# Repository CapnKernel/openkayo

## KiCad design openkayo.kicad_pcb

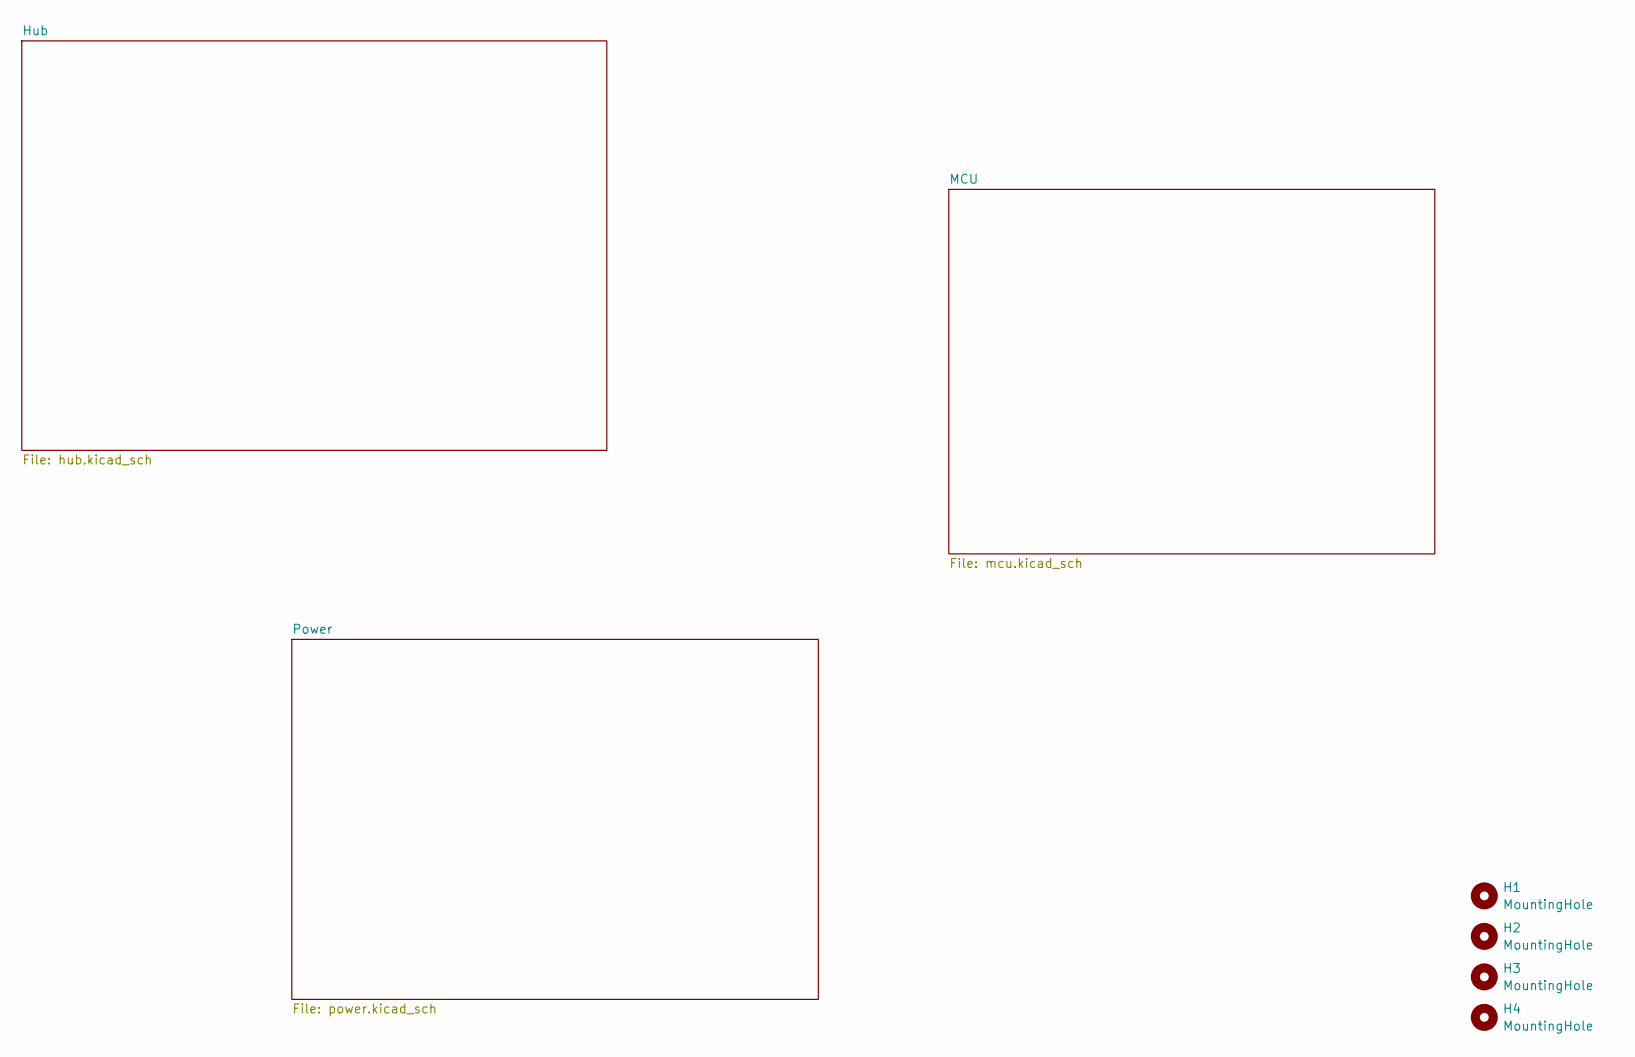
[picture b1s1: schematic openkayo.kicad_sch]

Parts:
H1, H2, H3, H4: MountingHole; MountingHole_3.2mm_M3

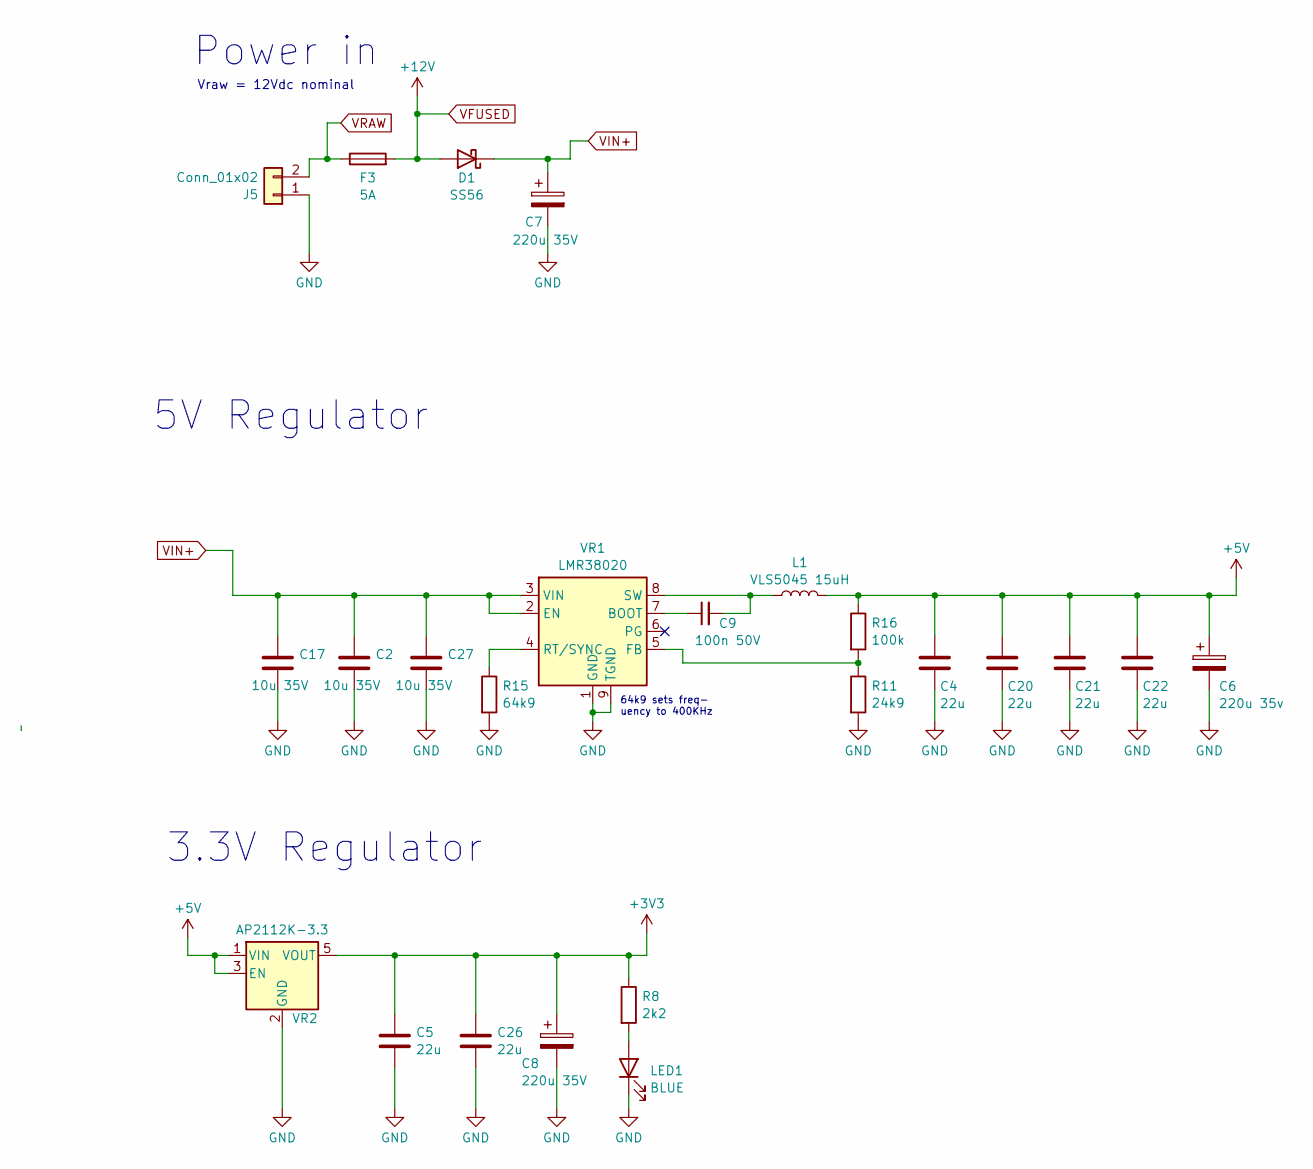
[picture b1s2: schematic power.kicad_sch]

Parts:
C2, C17, C27: 10u 35V; C_0805_2012Metric
C4, C5, C20, C21, C22, C26: 22u; C_0805_2012Metric
C6: 220u 35v; CP_Elec_8x10
C7, C8: 220u 35V; CP_Elec_8x10
C9: 100n 50V; C_0603_1608Metric
D1: SS56; D_SMA
F3: 5A; Fuseholder_Blade
J5: Conn_01x02; TerminalBlock_MetzConnect_Type086_RT03402HBLC_1x02_P3.81mm_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
L1: VLS5045 15uH; L_TDK_VLS6045EX_VLS6045AF
LED1: BLUE; LED_0603_1608Metric
R8: 2k2; R_0603_1608Metric
R11: 24k9; R_0603_1608Metric
R15: 64k9; R_0805_2012Metric
R16: 100k; R_0805_2012Metric
VR1: LMR38020; Texas_HSOP-8-1EP_3.9x4.9mm_P1.27mm_ThermalVias
VR2: AP2112K-3.3; SOT-23-5

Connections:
+3V3: C5.1, C8.1, C26.1, R8.1, VR2.5 (VOUT); also elsewhere on the board
+5V: C4.1, C6.1, C20.1, C21.1, C22.1, L1.2, R16.1, VR2.1 (VIN), VR2.3 (EN); also elsewhere on the board
GND: C2.2, C4.2, C5.2, C6.2, C7.2, C8.2, C17.2, C20.2, C21.2, C22.2, C26.2, C27.2, J5.1, LED1.1 (K), R11.2, R15.2, VR1.1 (GND), VR1.9 (TGND), VR2.2 (GND); also elsewhere on the board
unnamed: LED1.2 (A), R8.2
unnamed: C9.1, VR1.7 (BOOT)
unnamed: R11.1, R16.2, VR1.5 (FB)
unnamed: R15.1, VR1.4 (RT/SYNC)
unnamed: C9.2, L1.1, VR1.8 (SW)
VFUSED: D1.2 (A), F3.2; also elsewhere on the board
VIN+: C2.1, C7.1, C17.1, C27.1, D1.1 (K), VR1.2 (EN), VR1.3 (VIN)
VRAW: F3.1, J5.2

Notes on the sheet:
64k9 sets freq- uency to 400KHz
Power in
3.3V Regulator
5V Regulator
Vraw = 12Vdc nominal

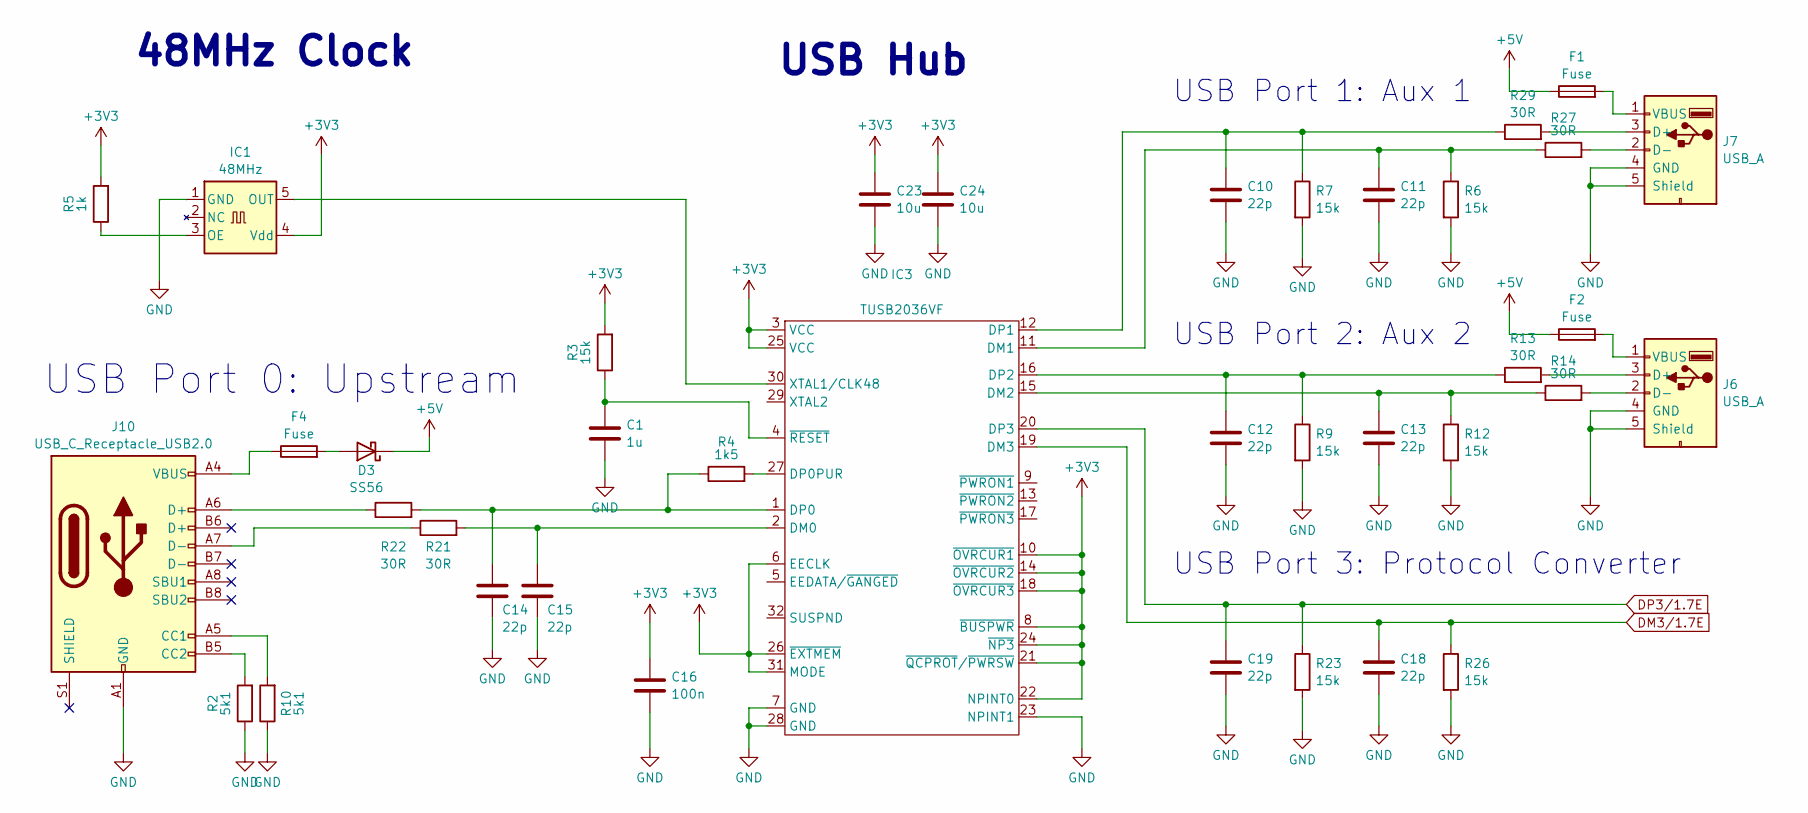
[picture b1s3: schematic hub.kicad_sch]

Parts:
C1: 1u; C_0603_1608Metric
C10, C11, C12, C13, C14, C15: 22p; C_0603_1608Metric
C16: 100n; C_0805_2012Metric
C18, C19: 22p; C_0402_1005Metric
C23, C24: 10u; C_0805_2012Metric
D3: SS56; D_SMA
F1, F2, F4: Fuse; Fuse_2018_5045Metric
IC1: 48MHz; SOT-23-5
IC3: TUSB2036VF; LQFP-32_7x7mm_P0.8mm
J6, J7: USB_A; USB_A_CONNFLY_DS1095-WNR0
J10: USB_C_Receptacle_USB2.0; USB_C_Receptacle_Amphenol_12401610E4-2A
R2, R10: 5k1; R_0603_1608Metric
R3, R6, R7, R9, R12: 15k; R_0603_1608Metric
R4: 1k5; R_0603_1608Metric
R5: 1k; R_0603_1608Metric
R13, R14, R27, R29: 30R; R_0603_1608Metric
R21, R22: 30R; R_0805_2012Metric
R23, R26: 15k; R_0805_2012Metric

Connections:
+3V3: C16.1, C23.1, C24.1, IC1.4 (Vdd), IC3.3 (VCC), IC3.6 (EECLK), IC3.8 (~BUSPWR), IC3.10 (~OVRCUR1), IC3.14 (~OVRCUR2), IC3.18 (~OVRCUR3), IC3.21 (~QCPROT/~PWRSW), IC3.22 (NPINT0), IC3.24 (~NP3), IC3.25 (VCC), IC3.26 (~EXTMEM), IC3.31 (MODE), R3.2, R5.2; also elsewhere on the board
+5V: D3.1 (K), F1.1, F2.1; also elsewhere on the board
DM3/1.7E: C18.1, IC3.19 (DM3), R26.1; also elsewhere on the board
DP3/1.7E: C19.1, IC3.20 (DP3), R23.1; also elsewhere on the board
GND: C1.2, C10.2, C11.2, C12.2, C13.2, C14.2, C15.2, C16.2, C18.2, C19.2, C23.2, C24.2, IC1.1 (GND), IC3.7 (GND), IC3.23 (NPINT1), IC3.28 (GND), J6.4 (GND), J6.5 (Shield), J7.4 (GND), J7.5 (Shield), J10.A1 (GND), J10.A12 (GND), J10.B1 (GND), J10.B12 (GND), R2.1, R6.2, R7.2, R9.2, R10.1, R12.2, R23.2, R26.2; also elsewhere on the board
unnamed: D3.2 (A), F4.2
unnamed: F4.1, J10.A4 (VBUS), J10.A9 (VBUS), J10.B4 (VBUS), J10.B9 (VBUS)
unnamed: IC1.3 (OE), R5.1
unnamed: IC1.5 (OUT), IC3.30 (XTAL1/CLK48)
unnamed: C15.1, IC3.2 (DM0), R21.2
unnamed: C11.1, IC3.11 (DM1), R6.1, R27.1
unnamed: C13.1, IC3.15 (DM2), R12.1, R14.1
unnamed: C14.1, IC3.1 (DP0), R4.1, R22.2
unnamed: IC3.27 (DP0PUR), R4.2
unnamed: C10.1, IC3.12 (DP1), R7.1, R29.1
unnamed: C12.1, IC3.16 (DP2), R9.1, R13.1
unnamed: C1.1, IC3.4 (~RESET), R3.1
unnamed: J6.3 (D+), R13.2
unnamed: J6.2 (D-), R14.2
unnamed: F2.2, J6.1 (VBUS)
unnamed: J7.3 (D+), R29.2
unnamed: J7.2 (D-), R27.2
unnamed: F1.2, J7.1 (VBUS)
unnamed: J10.A5 (CC1), R10.2
unnamed: J10.B5 (CC2), R2.2
unnamed: J10.A6 (D+), R22.1
unnamed: J10.A7 (D-), R21.1

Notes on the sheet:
48MHz Clock
USB Port 0: Upstream
USB Port 3: Protocol Converter
USB Hub
USB Port 2: Aux 2
USB Port 1: Aux 1

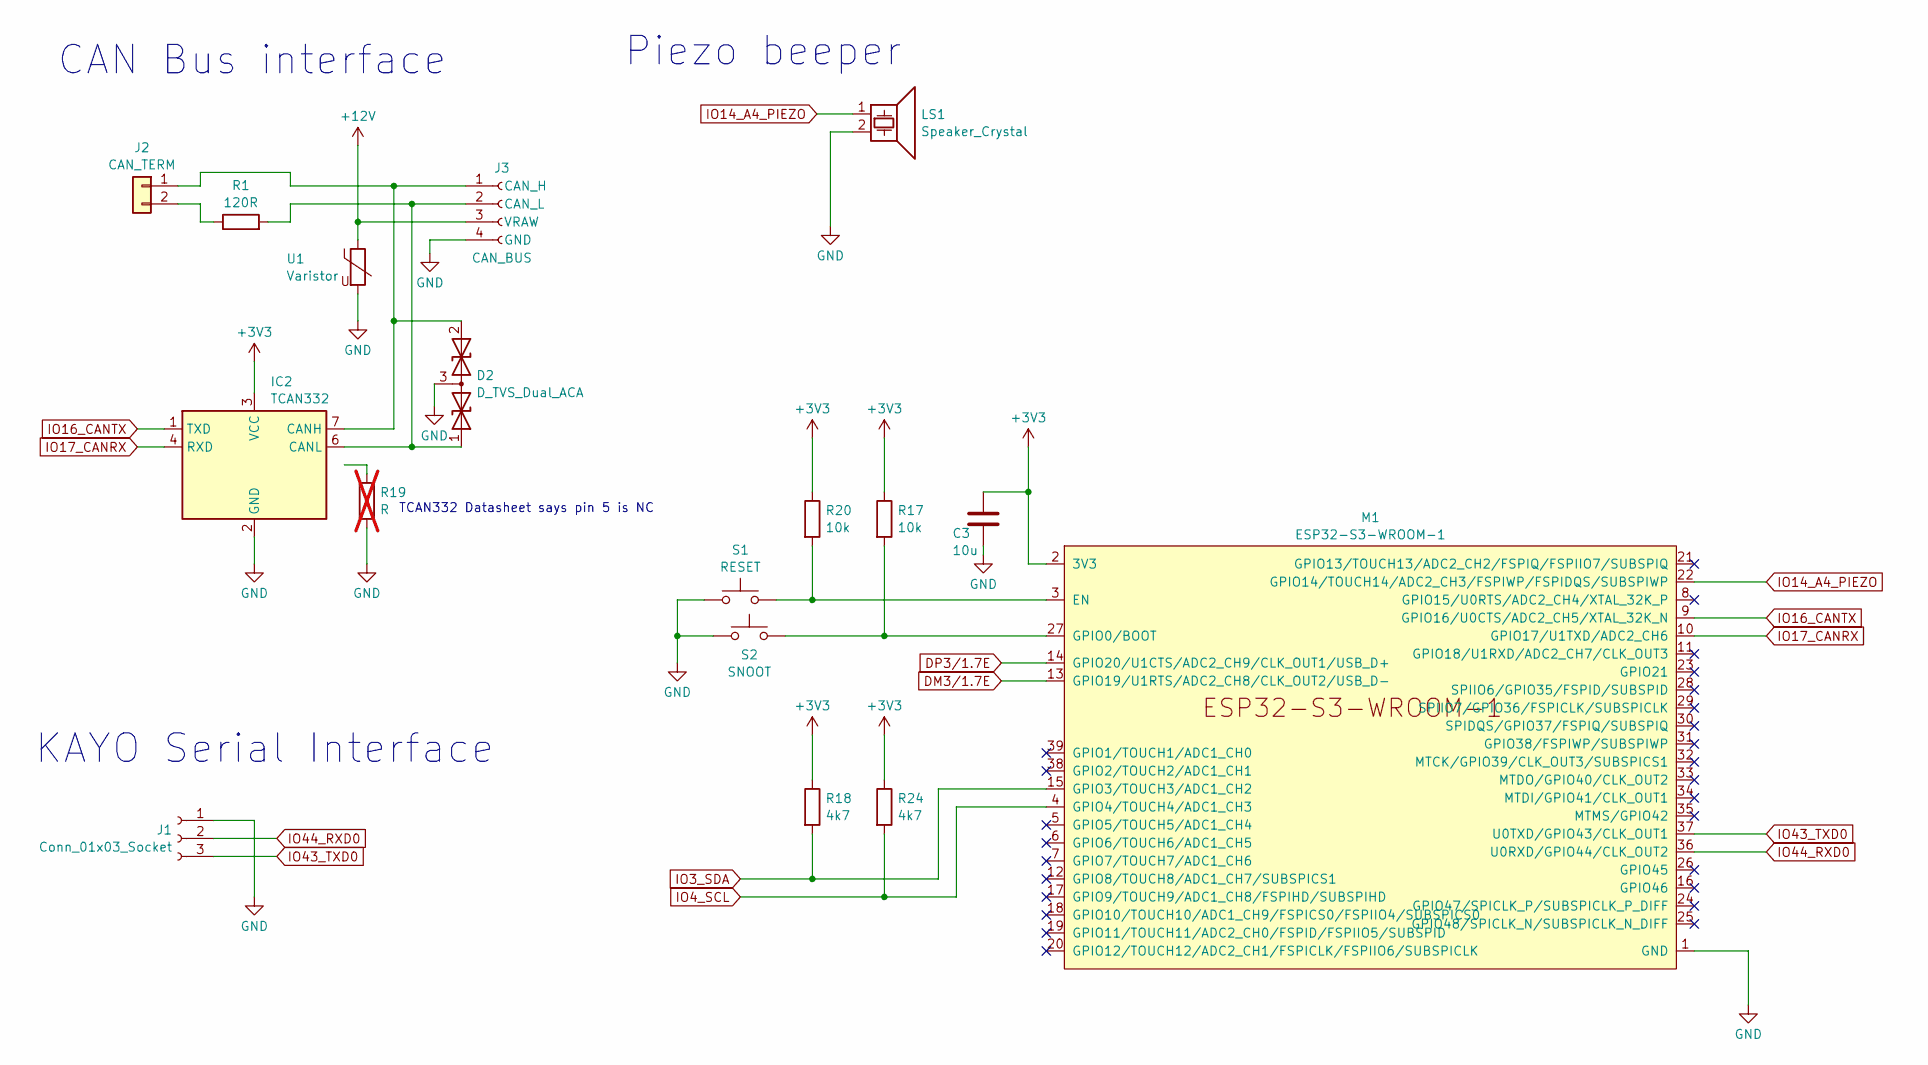
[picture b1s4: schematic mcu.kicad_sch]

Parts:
C3: 10u; C_0805_2012Metric
D2: D_TVS_Dual_ACA; SOT-23-3
IC2: TCAN332; SO-8_3.9x4.9mm_P1.27mm
J1: Conn_01x03_Socket; TerminalBlock_MetzConnect_Type086_RT03403HBLC_1x03_P3.81mm_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
J2: CAN_TERM; PinHeader_1x02_P2.54mm_Vertical
J3: CAN_BUS; TerminalBlock_MetzConnect_Type086_RT03404HBLC_1x04_P3.81mm_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
LS1: Speaker_Crystal; Buzzer_CUI_CPT-9019S-SMT
M1: ESP32-S3-WROOM-1
R1: 120R; R_2512_6332Metric
R17, R20: 10k; R_0805_2012Metric
R18, R24: 4k7; R_0805_2012Metric
R19: R; R_0805_2012Metric; not fitted
S1: RESET; SW_SPST_TL3342
S2: SNOOT; SW_SPST_TL3342
U1: Varistor; R_1210_3225Metric; LCSC C2935544

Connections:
+3V3: C3.1, IC2.3 (VCC), M1.2 (3V3), R17.1, R18.1, R20.1, R24.1; also elsewhere on the board
DM3/1.7E: M1.13 (GPIO19/U1RTS/ADC2_CH8/CLK_OUT2/USB_D-); also elsewhere on the board
DP3/1.7E: M1.14 (GPIO20/U1CTS/ADC2_CH9/CLK_OUT1/USB_D+); also elsewhere on the board
GND: C3.2, D2.3 (common), IC2.2 (GND), J1.1, J3.4 (GND), LS1.2, M1.1 (GND), M1.40 (GND), M1.41 (GND), R19.1, S1.1, S2.1, U1.2; also elsewhere on the board
IO3_SDA: M1.15 (GPIO3/TOUCH3/ADC1_CH2), R18.2
IO4_SCL: M1.4 (GPIO4/TOUCH4/ADC1_CH3), R24.2
IO14_A4_PIEZO: LS1.1, M1.22 (GPIO14/TOUCH14/ADC2_CH3/FSPIWP/FSPIDQS/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)
IO16_CANTX: IC2.1 (TXD), M1.9 (GPIO16/U0CTS/ADC2_CH5/XTAL_32K_N)
IO17_CANRX: IC2.4 (RXD), M1.10 (GPIO17/U1TXD/ADC2_CH6)
IO43_TXD0: J1.3, M1.37 (U0TXD/GPIO43/CLK_OUT1)
IO44_RXD0: J1.2, M1.36 (U0RXD/GPIO44/CLK_OUT2)
unnamed: D2.1 (A1), IC2.6 (CANL), J3.2 (CAN_L), R1.2
unnamed: D2.2 (A2), IC2.7 (CANH), J2.1, J3.1 (CAN_H)
unnamed: J2.2, R1.1
unnamed: M1.3 (EN), R20.2, S1.2
unnamed: M1.27 (GPIO0/BOOT), R17.2, S2.2
VFUSED: J3.3 (VRAW), U1.1; also elsewhere on the board

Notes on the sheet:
Piezo beeper
TCAN332 Datasheet says pin 5 is NC
CAN Bus interface
KAYO Serial Interface

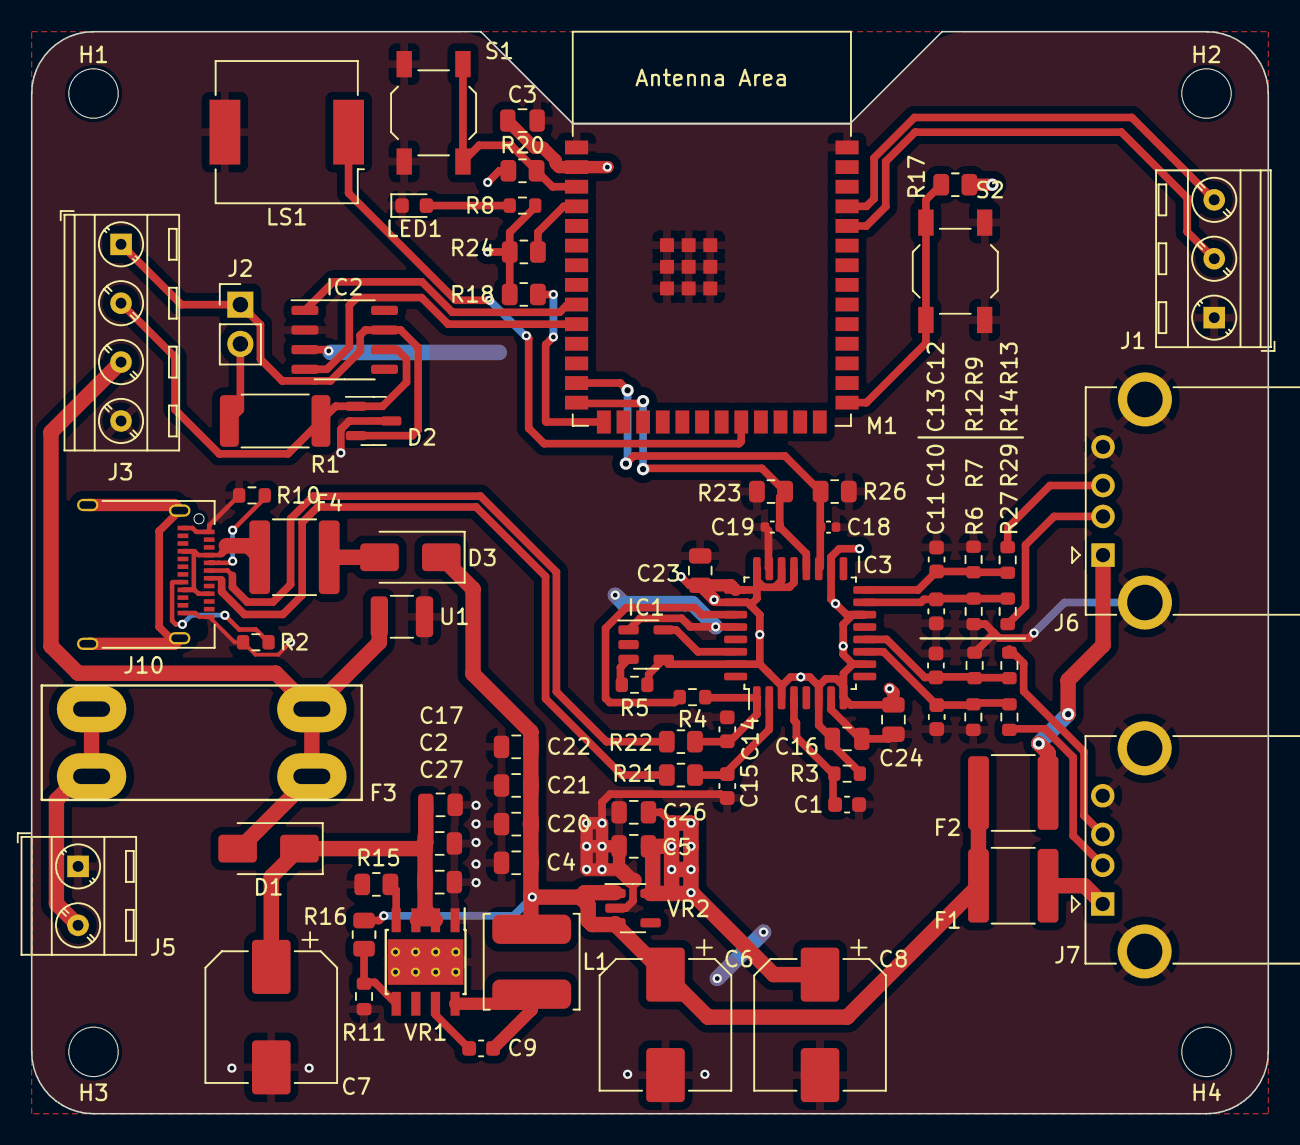
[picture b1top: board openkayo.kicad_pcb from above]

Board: 2 copper layers, 80.0 x 70.0 mm, 82 parts (0 on the bottom side), 47 nets.

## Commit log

2024-04-17 Update to KiCad 8.
2025-11-16 Updated to KiCad 9
2025-11-16 Added cutout in board outline for ESP32 antenna
2026-06-02 Added footprint for ESP32-S3-WROOM-1. Aligned in schematic.
